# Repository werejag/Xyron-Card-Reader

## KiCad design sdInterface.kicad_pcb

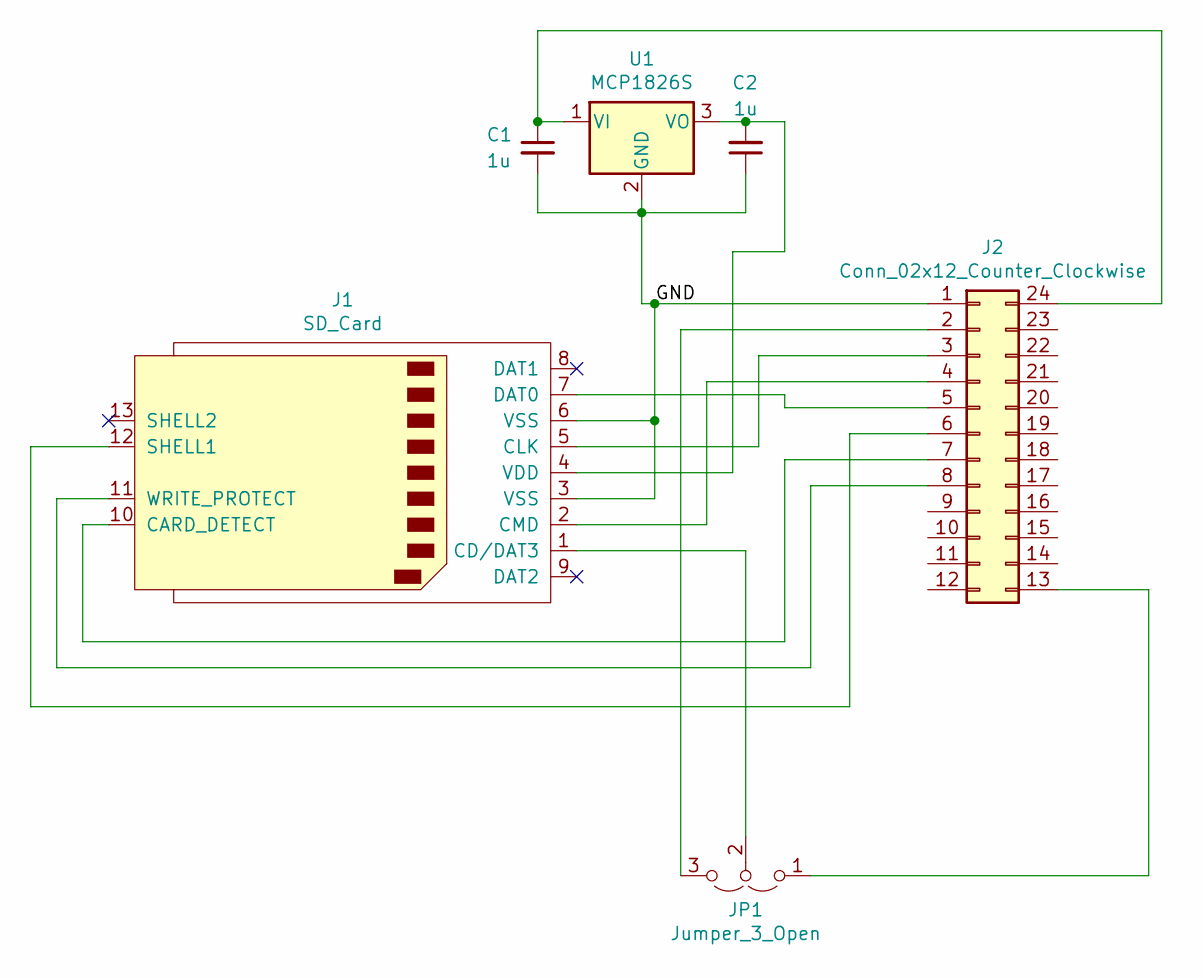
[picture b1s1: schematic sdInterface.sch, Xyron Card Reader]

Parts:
C1, C2: 1u; C_0805_2012Metric_Pad1.15x1.40mm_HandSolder
J1: SD_Card; SD_TE_2041021
J2: Conn_02x12_Counter_Clockwise; DIP-24_W15.24mm_Socket
JP1: Jumper_3_Open; PinHeader_1x03_P2.54mm_Vertical
U1: MCP1826S; SOT-223-3_TabPin2

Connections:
/GND: C1.2, C2.1, J1.3 (VSS), J1.6 (VSS), J2.1, U1.2 (GND)
unnamed: C1.1, J2.24, U1.1 (VI)
unnamed: C2.2, J1.4 (VDD), U1.3 (VO)
unnamed: J1.1 (CD/DAT3), JP1.2 (C)
unnamed: J1.2 (CMD), J2.4
unnamed: J1.5 (CLK), J2.3
unnamed: J1.7 (DAT0), J2.5
unnamed: J1.10 (CARD_DETECT), J2.7
unnamed: J1.11 (WRITE_PROTECT), J2.8
unnamed: J1.12 (SHELL1), J2.6
unnamed: J2.2, JP1.3 (B)
unnamed: J2.13, JP1.1 (A)

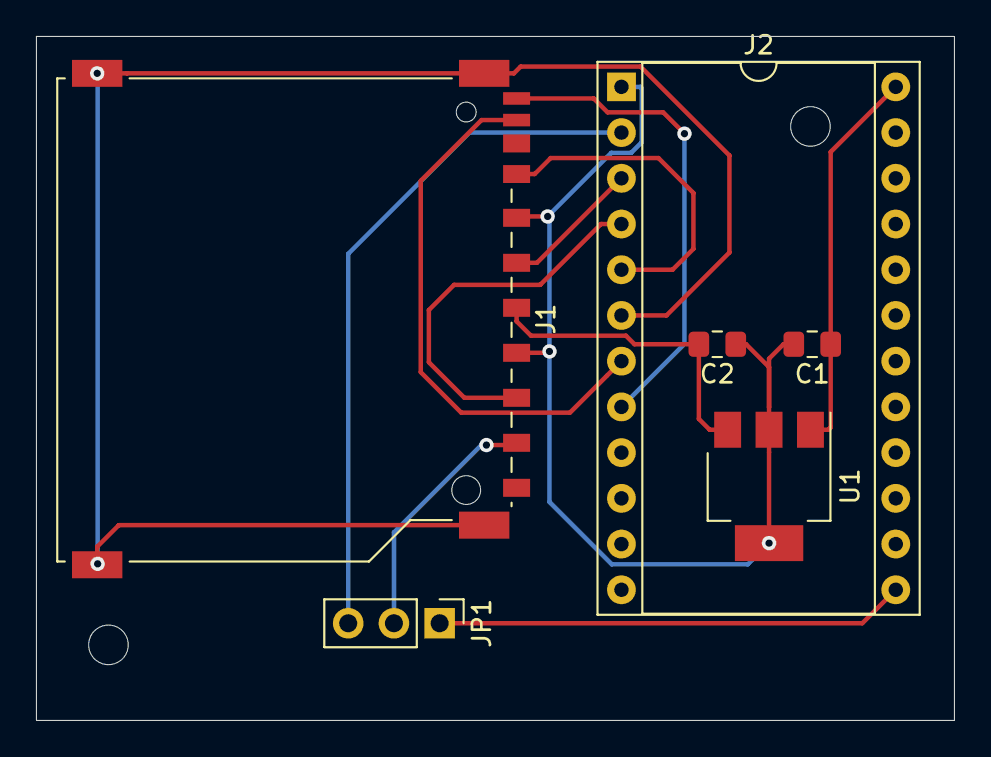
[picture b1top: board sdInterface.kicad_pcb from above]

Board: 2 copper layers, 51.0 x 38.0 mm, 6 parts (0 on the bottom side), 12 nets.

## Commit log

2020-01-25 Added 3.3v reg, JP1 now pins
2020-01-25 Flipped SD slot 180deg, Added 2mm mounting holes
2020-01-31 Added BOM
2020-02-26 Update sdinterface-bom.csv
    corrected sd card
